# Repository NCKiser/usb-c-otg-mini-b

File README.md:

This project converts a USB Mini-B port to USB Type-C (and/or USB Type-A), by use of either a USB "switch" or the TUSB320 IC from Texas Instruments.

The intent is to retain the OTG/DRP functionality of the Mini-B port while updating to the more modern Type-C (and/or more prolific Type-A) connector(s).

The "Single Port" design is intended to replace the Mini-B connector with a Type-C connector in situ, with minimal modification needed outide of removing the origial Mini-B port.

The "Double Port" design is intended as an adapter, plugging into the existing Mini-B connector, and bring the host functionality to the Type-A port, and the device to Type-C.

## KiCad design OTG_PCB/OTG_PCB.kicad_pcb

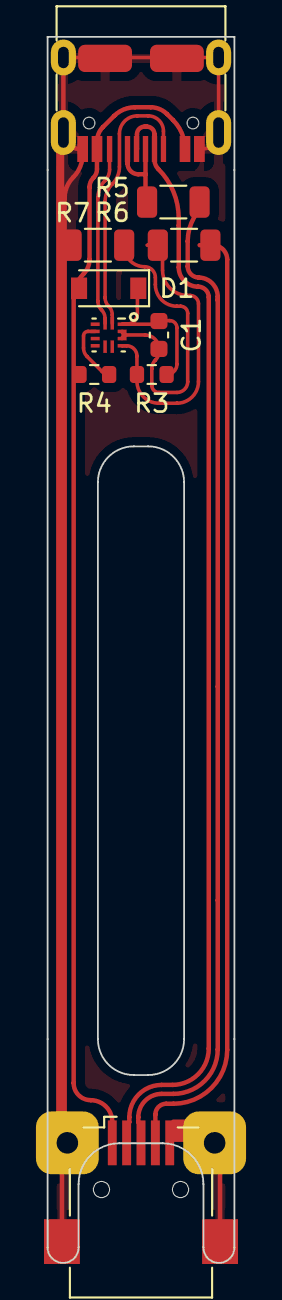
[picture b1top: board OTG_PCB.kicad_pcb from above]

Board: 2 copper layers, 10.4 x 68.3 mm, 10 parts (0 on the bottom side), 12 nets.

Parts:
C1: 100n; C_0603_1608Metric
D1: D_Small; D_SOD-123
J4: USB_MINI_B; USB_Mini-B_Wuerth_65100516121_Horizontal
J5: USB_C_Receptacle_USB2.0; USB_C_Receptacle_HRO_TYPE-C-31-M-12
R3: 200k; R_0603_1608Metric
R4: 900k; R_0603_1608Metric
R5, R6, R7: 0; R_1206_3216Metric
U2: TUSB320IRWBR

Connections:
+3V3: C1.2, D1.1 (K), R3.1, U2.12 (VDD)
CC1: J5.A5 (CC1), U2.1 (CC1)
CC2: J5.B5 (CC2), U2.2 (CC2)
D+: J4.3 (D+), R5.2
D-: J4.2 (D-), J5.A7 (D-), J5.B7 (D-)
ID: J4.4 (ID), R6.2
unnamed: J5.A6 (D+), J5.B6 (D+), R5.1
unnamed: R4.2, U2.4 (VBUS_DET)
unnamed: R3.2, R6.1, U2.9 (ID)
unnamed: C1.1, R7.1, U2.10 (GND), U2.11 (EN_N)
V+: D1.2 (A), J4.1 (VBUS), J5.A4 (VBUS), J5.A9 (VBUS), J5.B4 (VBUS), J5.B9 (VBUS), R4.1
V-: J4.5 (GND), J4.6 (Shield), J5.A1 (GND), J5.A12 (GND), J5.B1 (GND), J5.B12 (GND), R7.2

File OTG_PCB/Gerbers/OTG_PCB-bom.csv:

Id,Designator,Package,Quantity,Designation,Supplier and ref
1,U2,X2QFN,1,TUSB320LIRWBR,Texas Instruments PN: TUSB320L
2,D1,SOD-123,1,1N4148,
3,J5,USB_C_Receptacle_HRO_TYPE-C-31-M-12,1,USB_C_Receptacle_USB2.0,HRO Type C 31 M 12
5,C1,0603_1608Metric,1,100n,
6,R4,0603_1608Metric,1,900k,
7,R3,0603_1608Metric,1,200k,
8,"R6,R7,R5",1206_3216Metric,3,0 Ohm,

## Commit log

2022-08-30 Initial concepts
2022-08-30 Added some concept art
2022-08-30 Changed concept 2
2022-09-02 Single layer, flex only
2022-10-03 Added fabrication outputs
2022-10-03 Added fabrication output

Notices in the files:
parts and their libraries:
Copyright 2021 Accelerated Designs. All rights reserved.
